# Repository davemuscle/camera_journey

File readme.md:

# Camera Journey Nonrelease - FPGA

*Migrated to Git on February 20th, 2022. Original release on May 23rd, 2021*.

This is my first “nonrelease”: a self-project that has no good output. I didn’t really have a clear
vision or goal of the project going into this, so there were a few unexpected twists, turns, and
burns. I like to think the journey and the things you learn along the way are more important than
having a pretty product at the end. We’ll see.

The general timeframe for this project was between November 2020 to May 2021. A good “vertical
slice” of the project was finished before New Years, and I took a few breaks after that. I gave a
few weeks to play(?) Skyrim, a few weeks to play Valheim, some time to goof around with a Discord
bot in Python, and some time to speedrun video games. There were also a lot of nights of just not
wanting to do anything technical after getting off work.

| Youtube Videos |
| :--: |
| *Camera Journey Nightmare* |
|  |

## Journey's Start
It all started when I bought another FPGA board after the Fractal Project (link). Instead of getting
another Xilinx board, I decided I was going to go back to Altera with the DE10-Nano by Terasic.
Altera chips were the ones we used in school for learning digital logic / design.

|  |
| :--: |
| *DE10-Nano from Terasic* |

The DE10-Nano is a nice SoC (System-on-Chip) board from Terasic for $150. It’s an FPGA coupled with
a CPU on the same chip.

The FPGA is a fairly sizable Cyclone V, with 110K LEs (4-input logic elements). The FPGA
architecture can also make use of Altera’s 8-input logic elements called ALMs. Equivalently, you get
40K ALMs. It would be a good data point to benchmark these and compare them to the flagship 6-input
LUTs of the 7series parts.

The CPU is a dual-core ARM Cortex A9 running at 800 MHz. It’s accompanied with an awesome 3500 page
manual of register descriptions (much less fun and interesting than FPGA architecture, huh!). Altera
refers to this part of the SoC as the HPS, the Hard Processor System.

## Twist One: The Pocket Synthesizer

The initial idea of the project was to make a handheld audio synthesizer. I’d slap a PCB with an
audio codec, a mini LCD, and a suite of input directly on top of the 2x20 male headers. I quickly
designed the schematic in KiCad, but ran into size constraints when picking out parts on DigiKey. If
it couldn’t have all the buttons I wanted, I wasn’t interested. So eventually this idea fizzled out.
The screenshot below is how far I got in the layout process of the PCB.

|  |
| :--: |
| *Plug-in Synthesizer End* |

## Twist Two: The Single Camera

I’ve had some experience working with camera modules, namely the OV5640 from Omnivision. I decided
that hooking up one of these to the DE10-Nano and then implementing some real-time video effects via
FPGA would be fun. I ended up buying one of Waveshare’s camera modules for $25. These versions of
the OV5640 are easier to use since they send data over a parallel video port, instead of MIPI.

|  |
| :--: |
| *Waveshare OV5640* |

The basic data flow idea was to have the camera send a raw 1920x1080 pixel stream at ~30 FPS into
the FPGA, buffer it, convert the Bayer sensor data to RGB, and send it to the HDMI sink. Here's the
hardware that had to be written to get the camera feed to show up on a TV or monitor:

|  |
| :--: |
| *FPGA Block Diagram for Single Camera Setup* |

- **OV5640 Controller**
    - Main controller that drives the design. It contains an SCCB (I2C) driver and a FIFO for sending register reads and writes to the camera during run-time. I had to rewrite the I2C driver used in the ADV7513 controller because Omnivision are dumb hacks. They copied the I2C bus and renamed it to SCCB to avoid paying royalties to Phillips. Problem with that is their device easily holds the bus hostage unless you give it special treatment.
- **DVP to AXI Video**
    - The start of the video datapath. Converts a parallel video port (HREF, VSYNC, 8 data bits) into AXI Video (SOF, EOL, Valid, 8 data bits).
- **Framebuffer**
    - Video buffering to provide a constant output stream at 1080p 60 FPS. Fun to design because there were three clock domains to handle.
- **Debayer**
    - Performs image demosaicing with multiple 5x5 sliding kernels. Converts raw sensor image data into the RGB colorspace
- **AXI Video to VGA**
    - Converts AXI video into VGA (HSYNC, VSYNC, DE, 24 data bits).
- **ADV7513 Controller**
    - Final output of the design. I2C commands initialize the ADV7513 chip by Analog Devices onboard the DE10-Nano. This handles the TMDS encoding and serialization of the VGA stream. Pretty easy chip to use and it's well documented.

## The Fun of Cameras

Like most other camera sensors, the documentation for the OV5640 is horrible or nonexistent. The
register maps have tons of hidden/reserved registers that are actually needed to get it to function
well. The manufacturers hide these registers expecting companies to purchase thousands of their
camera sensors, and sign an NDA with them for a user guide. Even after that, the user guide is in
broken English, and only works for certain camera setups. If you need to change camera settings or
resolutions, have fun. Although sparse, there is good documentation and drivers from users floating
around on Github and EEVblog. I had to spend a while to get these registers right, so I'm including
them in the references.

## The Framebuffer and the HPS

The most difficult part of the design was the frame buffering. Because standard monitors won’t
accept 1080p at 30 FPS, and because the camera frame rate isn’t exact, the input stream needs to be
buffered and read out at 1080p at 60 FPS. The answer to this is the triple-buffered frame buffer.

|  |
| :--: |
| *Framebuffer Design* |

For an uncompressed raw Bayer stream at 8 bits, that’s (1920\*1080\*8) 16.5 Mbits. The FPGA definitely
does not have enough block RAM for three frames of that. We could use the JPEG format on the camera
sensor to reduce this, but I don’t want to imagine the horror of getting that setup. We could also
do the JPEG encoding/decoding in the FPGA, but for some reason I didn’t want to do that (in
retrospect, it’s not a bad idea). This leaves the only available memory option as the DDR3 onboard
the DE10-Nano.

The idea of my framebuffer is to have three buffers being used in memory. Two buffers will always be
used for writing, and one for reading. The arbiter manages the buffers such that the one being read
from is never written into.

The memory controller allows a wide data width of 256 bits, so incoming pixels are packed up and
written into the first asynchronous FIFO. A pulse is driven and syncronized to the memory clock
domain telling the arbiter to start moving that line into the DDR3. Once a full frame is written,
the arbiter allows a downstream timer to read lines at the rate required for the output resolution.
The output pixels are unpacked and then sent downstream.

Accessing the DDR3 from the FPGA on the Cyclone V is a bit strange, and it was definitely a
challenge for me. At this point I had written all the RTL for the FPGA, and hadn’t even touched the
HPS. The only way to access the DDR3 through the FPGA is to get the HPS programmed and have it
enable the bridge from the hardened memory controller to the FPGA, so here we go.

If you want to use the HPS in your FPGA design, you need to instantiate it as a component in Qsys.
Qsys is comparable to Xilinx’s IP integrator for block designs. I didn’t want to take any chances,
so I modified the Qsys file given by the golden reference design by Terasic. The part of note when
creating the Qsys was enabling the fpga2sdram bridge. This gives the FPGA access to the memory
controller. I programmed the SDcard given with the DE10-Nano with Terasic’s known-good image for
DDR3 communication, and was ready to go.

|  |
| :--: |
| *Qsys Instantiating the HPS* |

My first iteration of the framebuffer used the Avalon interface to talk to the SDRAM controller.
Avalon is much simpler compared to AXI: there are a lot less signals and it’s pretty easy to
implement. My main problem with it was that the memory controller would lock up if I tried to do
even small bursts, like a burst of 8. So my design could only request one transaction at a time.
This was fine because of the interface's wide bus width of up to 256 bits.

I now had a real-time camera stream going to my TV from the OV5640. After adding a weird
font-overlay controller in RTL, I made a backup of the project, and took a break. This was on
December 31st 2020. Unfortunately I never recorded a demo video of this stage of the project, since
I didn’t think much of it.

After taking a break for maybe a month, I decided to come back and make some upgrades. I rewrote the
framebuffer entirely, made it more modular, and converted the bus from Avalon to AXI. This means I
had to change the fpga2sdram bridge in the HPS from Avalon to AXI. I also added in memory addressing
options, to provide vertical and horizontal effects like splitscreen, flip, mirror, and scrolling.

## The Preloader and U-Boot

I came across a major problem with my upgraded framebuffer -- I couldn’t write to it! The SDRAM
controller was never responding to my ‘awvalid’ requests. With some research, I decided that the
problem was because I needed to update the preloader or update U-Boot for the HPS. Below are
conceptual designs for the most important hardware chunks of the fractal engine: the fractal slice,
and the fractal core. 

The Cyclone V has a pretty involved boot process. First it reads from an onboard ROM for boot
information, then it reads from the preloader within the SDcard, then it reads from U-Boot, which is
also in the SDcard. After that, it finally loads up Linux.

Apparently, if you make some drastic changes to the HPS in Qsys, you need to subsequently update the
preloader, whoops! I started reading documentation on building embedded linux for the Cyclone V, and
tutorials from Rocketboards on rebuilding the preloader. Nothing was working for me though. I
downgraded my Quartus and SoC EDS versions to match what was used for the reference design, and
tried a whole suite of things. All the tutorials I was looking at were using Linux to rebuild the
preloader, and I was working in Windows, so I chalked it up to that.

There is a single post on the Intel forums that is dealing with this issue, where the AXI writes
don’t respond. In that post they say to update the preloader or update U-Boot: so it was time to try
U-Boot.

|  |
| :--: |
| *Intel Forum Post* |

After looking into how U-Boot works, I plugged in the USB cable from the DE10-Nano into my PC,
opened PuTTy as a serial port at 115200 / 8bits / no parity, and booted it up. I pressed a key to
stop the autoboot and typed in “printenv” to see the U-Boot setup. U-Boot uses a bunch of
environment variables stored in the SDcard to configure the HPS after the preloader. To my surprise,
this fpga2sdram_handoff variable seemed funky.

According to the Cyclone V manual, the AXI bridges require two ports (compared to Avalon bridges
requiring one port) of the SDRAM controller. The default U-Boot script was holding my AXI port in
reset!

|  |
| :--: |
| *U-Boot Environment Variable Snippet* |

|  |
| :--: |
| *Cyclone V Holding My AXI Port Hostage!* |

I added a single line to my U-boot script and placed it on the SDcard. Done, my upgraded framebuffer
was working great.

|  |
| :--: |
| *Fixed U-Boot Script* |

## Image Processing Verification Tools

To make verification of my video processing blocks better, I designed some VHDL blocks to easily
facilitate passing image data through a testbench. I use a MATLAB script to convert RGB images from
any filetype into a flattened text file of integers. The image_reader block within the
pattern_generator block reads this text file and provides it as an AXI video stream. The pattern
generator can also give counting patterns, or two types of standard color bars. 

The image data is passed through the DUT and then sent into the image_writer block, producing
another text file. Outputs are given to stop the testbench when a certain number of images have been
written. I then have another script in MATLAB that converts the text file back to an image, and
plots it on the screen. It can then be visually inspected to verify RTL image processing.

The image_writer and image_reader blocks accomplish this by using std.textio library to read and
write files. The way I’m using the std.textio library here is not synthesizable. This is meant only
for simulation. However, you can synthesize with this library! But it’s only to initialize BRAM, it
only works in Vivado, and it only works if the text files are of the bit_vector type. I did this in
my 96-Note Spectrum Analyzer.

|  |
| :--: |
| *Testbench with Image Verification Suite* |

|  |
| :--: |
| *You can get some pretty funky outputs with a buggy FPGA design! This was created due to a FIFO underflow while simulating my debayer block.* |

## Python Control via UART

An interesting idea I had for debugging my FPGA designs was to hook up a UART-USB converter and use
PySerial to send scripted reads/writes over a serial port. I picked up a converter from Digilent and
wrote some RTL for a UART driver. 

|  |
| :--: |
| *Digilent's PMOD UART to USB* |

Writing the RTL for serial interfaces like I2C, SPI, and UART are easy enough. The major part that I
overlooked was how UART expects bits LSB first, but pretty quickly I could read and write a register
using Python code. I set up a basic communication structure with byte stuffing so that PySerial
could send packets, giving it 32-bit access to a 16-bit address space.

I then came up with a commenting format, which would be written inside the VHDL register file. The
comments would describe various register descriptions, bit fields, and address offsets. A different
Python script would parse through the register file, and auto-generate a suite of classes that could
be imported and used for easily accessing FPGA registers without having to remember address offsets
or bitfield locations.

Description | Image
:--: | :--: 
VHDL Register File with Comments for Parsing |  
Generated FPGA Class |  
Generated Register Class | 
Using iPython | 
Help Command for the FPGA | 
Help Command for the Registers | 
iPython with tab auto-completion | 
Writing to all 32-bits of a register | 
Writing to a single bitfield of a register | 

Was there a better way to do this? For sure. If I ever decide to use Python again for this, I’ll use
XML-type formatting in the RTL to standardize things instead of using my own format. Is this kind of
an abuse of the Python class construct? Ha, yeah!

## Twist Three: The Double Cameras
One of the main projects floating around online for the DE10-Nano is a “Real-time HDR Video”
project. It’s even packaged with the System-CD by Terasic. The idea involves feeding two camera
streams into the FPGA with differing exposure settings. The streams are then mixed together to give
a single feed but with a higher dynamic range. I decided I wanted to do something similar. Maybe use
two cameras to emulate our brain’s depth perception, or do some parallax effect.

I designed a PCB in KiCad to hold two cameras, sent it off, and had it back in a week or so. It’s a
really simple board that just plugs into one of the 2x20 headers on the DE10-Nano, and then two
Waveshare cameras plug into the PCB to give two streams. When I made the PCB, I also included a
design to hold four cameras, just in case I wanted to try and do something with 360 degree coverage.

 | 
:--: | :--:
*Camera Board PCB* | *Dual Camera Board in Action*

The PCB worked fine, but the Waveshare camera modules definitely were not behaving the way I
expected. Two OV5460 camera modules with the same external input clocks, same I2C inputs, and same
register initializations do not behave the same way!

My first approach to fix this was using an asynchronous FIFO to match the rates, IE: if one camera
sent their start-of-frame 10 clocks early, then it was delayed and the proper CDC was applied to
make sure the streams lined up. The biggest problem with this was the skew between frames. Both
cameras need to be running at exactly the same FPS, and that just won’t happen. Eventually the skew
would cause the FIFO to overflow, and then it’s over. The reference project does some hack where
they lower the external clock rate of one camera for a short amount of time, but I don’t like that.

 | 
:--: | :--:
*Dual Camera Skew* | *Awful Camera Noise*

The best solution for me would be to upgrade the framebuffer to support multiple channels. So I did.
But then Qsys reported the HPS couldn’t support multiple AXI channels, so I’d need to either write
an interconnect or downgrade back to the Avalon bus. This annoyed me, so I started evaluating
options.

The quality of the camera streams wasn’t even good: they were filled with intensive raw pixel noise.
Even my work with just one of the camera modules suffered from this. I tried tons of register
configurations and couldn’t get the noise to go away. The OV5640 manual lists a maximum of 3.0V on
the digital IO, but Waveshare is driving them with 3.3V, maybe that’s it? The horrible Waveshare
board is also driving IO pins directly to 3.3V and GND (seriously, look that up), maybe that's it?
The DVP mode is a parallel video bus running at ~80 MHz, so there is probably extreme crosstalk
happening between the data bits, maybe that’s it? 

Either way, I wasn’t too excited about working more with these camera modules. It was time to move
on. At least I had got my demo to the point of being able to switch between camera streams. In the
GIF below you can see the parallax effect for a flash drive closely in front of both cameras. This
is the same thing as putting your thumb in front of your face, then alternating between which eye
you have open.

:--:
*Camera Parallax*

## Twist Four: The IP Camera

This DE10-Nano board has a few interesting peripherals connected only to the HPS: ethernet, USB-OTG,
and an accelerometer. So far, the entire project hasn’t touched these because I’ve stayed away from
the HPS. Not anymore, I’m diving right in!

The new idea was to buy an IP camera from Amazon, plug it into the ethernet port on the DE10-Nano,
and have a Linux image loaded onto the ARM CPU to pull from the camera. I could then use the FPGA to
apply video effects, then send it over the USB port to my PC as a UVC Webcam.

I bought a cheap camera, plugged it into my router, and logged into its HTML page. This was so
refreshing just being able to mouse around and change the camera settings, instead of sending
commands over an I2C bus! I made sure the camera wasn’t DOA by viewing the feed in Internet
Explorer.

:--:
*IP Security Camera*

After making sure the IP address was static, I connected the camera directly to the DE10-Nano and
started poking around in Linux. I wanted to see packets being sent that carried the video data, even
if I couldn’t view the frames. I used ifconfig and tcpdump to try and read packets. The main thing I
could see was the camera asking for a MAC address over ARP.

:--:
*Viewing Packets and ARP Requests*

Even after making sure the ARP was set up correctly, I could tell the camera wasn’t sending enough
data for a video stream. So there is some initialization that needs to happen here. I put the camera
back into the router, and used Wireshark on my main PC to see what was happening.

 | 
:--: | :--:
*Slow Packets with No Video | RTSP Packets using UDP to Send Video*

I determined that I shouldn’t be thinking about this in such a low-level way. Eg: I don’t need to
manually construct the TCP packets to initialize this. There is already software to do it all. With
research, FFmpeg seemed like the way to go.

## H264 and FFMPEG

FFMPEG is a FOSS library for performing various video processing applications. Most specifically,
with the installation of libx264, it could read H.264 encoded video over an RTSP stream. This is
exactly what my camera is sending, so I started working on getting FFmpeg installed.

The Linux distribution that Terasic gives with the System-CD is Angstrom. I tried using ‘opkg’ to
install FFmpeg, but it wasn’t giving me anything usable. I also didn’t see an option for libx264. So
I decided to compile it from source.

I used GIT to pull both sets of source codes, and started running Makefiles. I followed some
instructions online and had to manually modify a few paths. Libx264 compiles pretty quickly, but
FFmpeg was taking a few hours. FFmpeg also failed about an hour due to memory constraints, so I
plugged in a 16GB flash drive, mounted it in Linux, and compiled it under there. Eventually I had a
usable FFmpeg binary.

**Editor's note 02/20/2022: Cross compiling here would have been a better choice**

:--:
*Compiling FFmpeg with an SD card*

FFmpeg could now pull a single frame from the camera and convert it into JPG. I opened an SFTP
session within MobaXterm to view the image over windows by just double clicking it. Even if it’s out
of focus, it’s looking good! Much less painful than the OV5640. I also tested FFmpeg by converting a
view seconds of the stream into an MP4, and it worked decently well. It was a bit slow though.

:--:
*Capturing a Still with FFmpeg*

:--:
*Bonus: Security camera trying to send data back to China. Hope you enjoyed the bathrobe show.*

## Hardware Software Bridge

The next step was to get the IP camera feed to show up on my HDMI monitor/TV. This required
functional communication between the HPS and FPGA. I quickly converted my framebuffer into a
framestreamer, which would only read from the DDR3 and let the HPS fill the memory with what should
be shown on the screen. I also added some AXI ports in the Qsys to allow the HPS to control the
framestreamer parameters like the frame offsets, which frame number is active, and the resolution of
the frame. These AXI ports would connect the FPGA to the HPS via the “lighweight AXI bridge”, which
was viewable in the device tree.

:--:
*Simpler FPGA Design to Leverage SW*

It was quite a breath of fresh air writing C code for this. I memory mapped the lightweight bridge,
and three portions of memory in DDR3 for the three triple-buffered frames. My first check was to
fill that image-space and make sure it would show up on the screen. On my Windows PC I converted a
JPG image to a binary file, then used C code on the DE10-Nano to write the binary file into DDR3
memory. The output is below.

:--:
*C code snippet to copy the binary file into shared SDRAM*

:--:
*HW SW Bridge in Action: Software Sets Up the Image, Hardware Displays it*

## Journey's End

Things fell apart when I wanted to see the real-time security camera video on the monitor. The ARM
CPU was just not keeping up with the requirements to read the RTSP packets, decode the H264 stream,
and convert it to raw RGB video. I checked the CPU usage with “htop”, and both were at 100%. The
FPGA also wasn’t helping, because it has to take priority over the memory controller to read the
frames at a constant rate. Since the memory controller arbitrates access to the FPGA and HPS, there
is some slowdown here. Even with a lower resolution I couldn't get a good output.

I had hit the limit, and was out of ideas. This camera was definitely not right for the project
goals (if there ever were any), and I had enough with the twists and turns, so I called it quits.
The video shown at the top and on the front page was the farthest I got with this camera. There were
definitely still improvements needed to the C code and FPGA design.

I take a lot of pride in having the grit to push through issues and never giving up, but the idea of
moving on and doing something new is too exciting. So this marked the end of the camera journey.

 | 
:--: | :--:
*IP Camera Setup to DE10-Nano Embedded Linux* | *Glitchy, High Latency, ~1FPS IP Camera Output*

## In Retrospect

Here are various things that I got some exposure to, designed, or enjoyed doing:
- Serial interfaces like UART and I2C 
- Debayer RTL block
- Framebuffer RTL block
- Asynchronous FIFOs, handshake-based pulse synchronizers, CDC with >2 clock domains
- Video verification techniques, testbench improvements
- Python generated classes for FPGA control
- Quartus flow (even if it was just clicking in the GUI)
- Quartus Qsys Design, using Altera IP (PLLs)
- U-Boot
- Embedded Linux
- Basic Networking (I'm still a baby - but this was good to learn)
- Real C-code (memory mapping, malloc, free)

Here are some of the ideas I had that didn't pan out, or that I didn't get to:
- Ray-tracing
- Face Detection via Viola Jones (did a lot of MATLAB studying on this, but struggled with it. Neural network next time)
- Real-time Video Fx in RTL
- Stereoscopics

Here are some of the things I didn't like:
- Altera/Intel Documentation, lack of active forum compared to Xilinx
- Cyclone V preloader issues

**Editor's Note, 02/20/2022: Looks like Xilinx forums are going in a similar direction?**

## Downloads
- [OV5640 Init Sequence for 1080p DVP Mode](/doc/ov5640_init.txt)
- [ADV7513 Init Sequence for DE10-Nano at 24-bit RGB 1080](/doc/adv7513_init.txt)

## References
1. [Terasic, DE10-Nano Kit Downloads](https://www.terasic.com.tw/cgi-bin/page/archive.pl?Language=English&No=1046&PartNo=4)
2. [Analog Devices, ADV7513 Programming Guide](https://www.analog.com/media/en/technical-documentation/user-guides/ADV7513_Programming_Guide.pdf)
3. [Waveshare (hooligans), OV5640 Board](https://www.waveshare.com/wiki/OV5640_Camera_Board_(B))
4. [Sparkfun, OV5640 Manual](https://cdn.sparkfun.com/datasheets/Sensors/LightImaging/OV5640_datasheet.pdf)
5. [Xenpac/sun4csi, Great OV5640 Driver](https://github.com/xenpac/sun4i_csi/blob/master/device/ov5640.c)
6. [Standford, High-Quality Linear Interpolation For Demosaicing of Bayer-Patterned Color Images](https://stanford.edu/class/ee367/reading/Demosaicing_ICASSP04.pdf)
7. [Altera, Avalon Bus Spec](http://www1.cs.columbia.edu/~sedwards/classes/2011/4840/mnl_avalon_spec.pdf)
8. [ARM, AXI Bus Spec](http://www.gstitt.ece.ufl.edu/courses/fall15/eel4720_5721/labs/refs/AXI4_specification.pdf)
9. [Intel Forum, How can I enable the FPGA2SDRAM bridge on Cyclone V SOC devices?](https://www.intel.com/content/www/us/en/support/programmable/articles/000086918.html)
10. [Criticallink.com, Important Note about FPGA/HPS SDRAM Bridge](https://support.criticallink.com/redmine/projects/mityarm-5cs/wiki/Important_Note_about_FPGAHPS_SDRAM_Bridge)
11. [Oguz Meteer, Building embedded Linux for the Terasic DE10-Nano](https://bitlog.it/20170820_building_embedded_linux_for_the_terasic_de10-nano.html)
12. [Altera, Cyclone V HPS TRM](https://www.intel.com/content/dam/www/programmable/us/en/pdfs/literature/hb/cyclone-v/cv_54001.pdf)
13. [Wimsworld, New FFMPEG install on BeagleBone Black](https://wimsworld.wordpress.com/2013/06/26/new-ffmpeg-install-on-beaglebone-black/)
14. [Batchloaf, A simple way to read and write audio and video files in C using FFmpeg](https://batchloaf.wordpress.com/2017/02/12/a-simple-way-to-read-and-write-audio-and-video-files-in-c-using-ffmpeg-part-2-video/)

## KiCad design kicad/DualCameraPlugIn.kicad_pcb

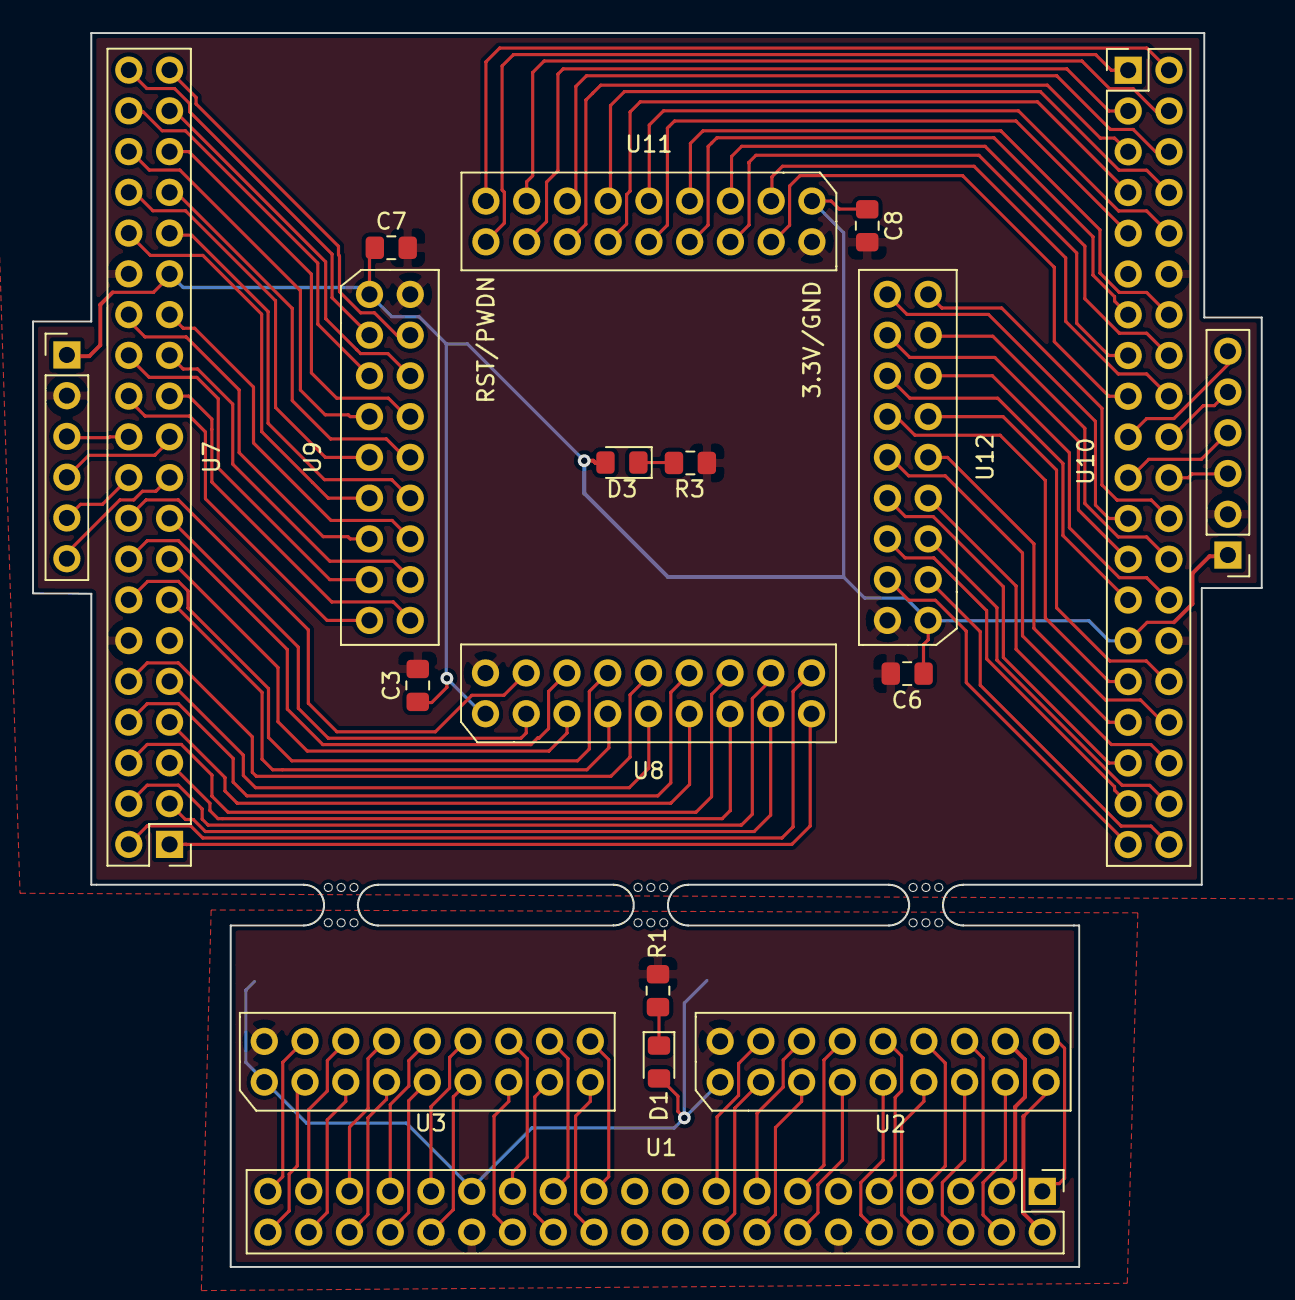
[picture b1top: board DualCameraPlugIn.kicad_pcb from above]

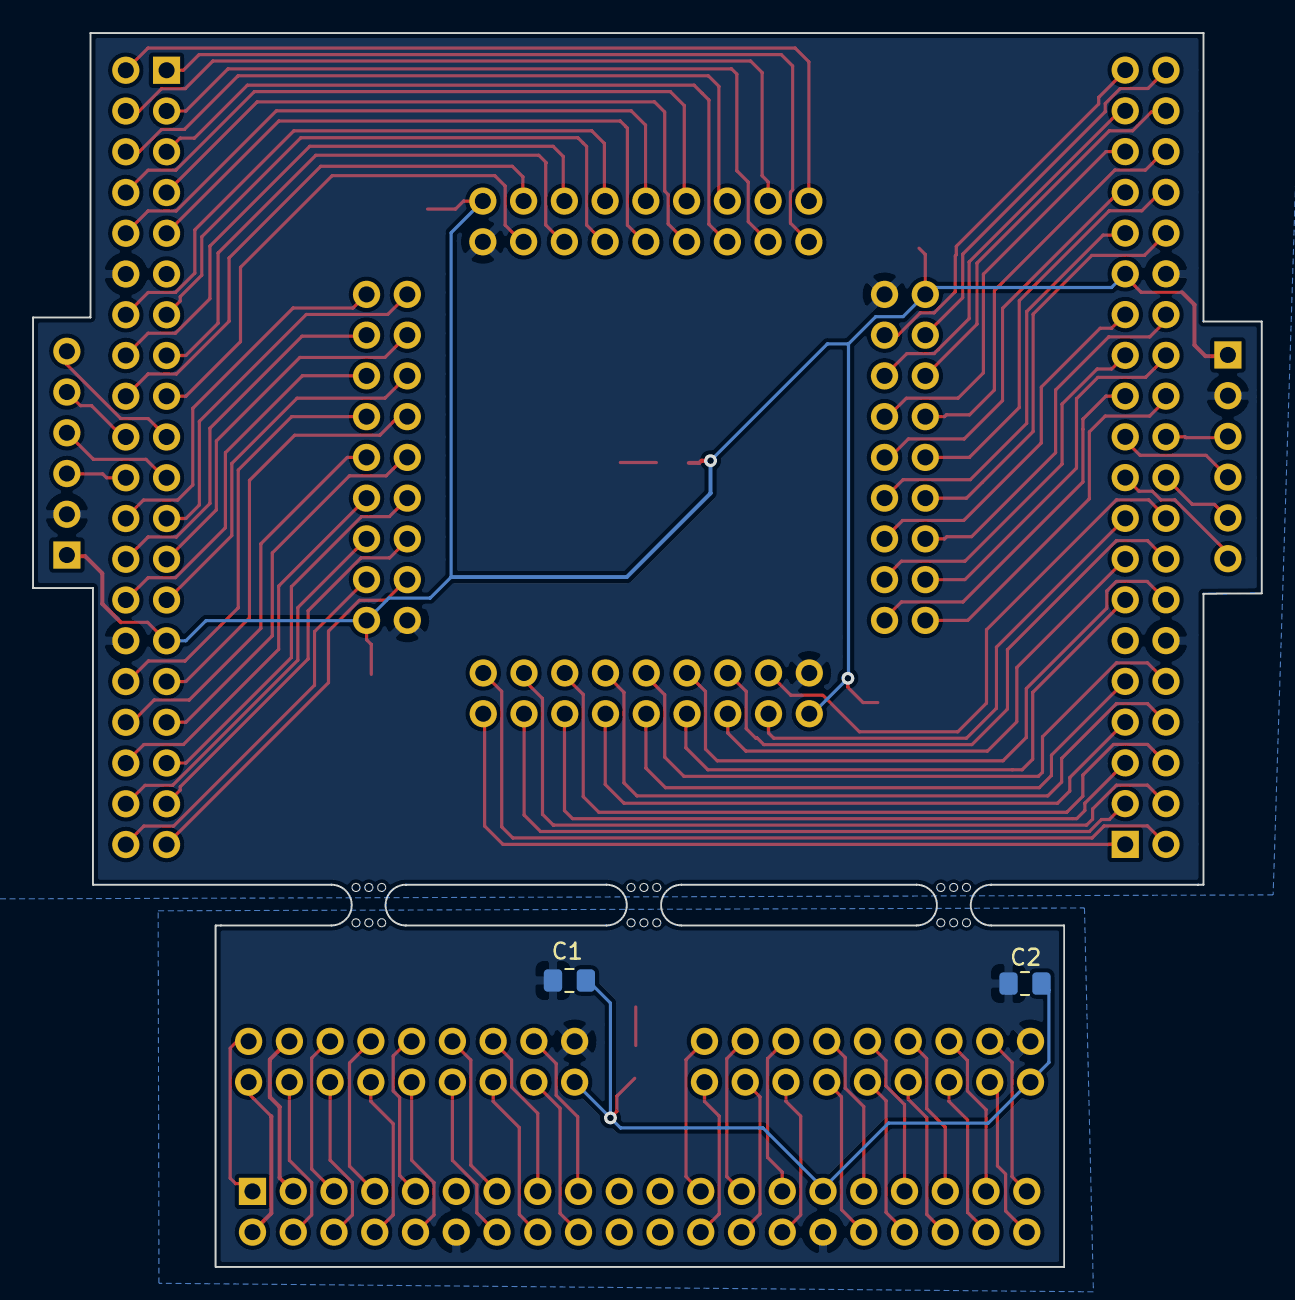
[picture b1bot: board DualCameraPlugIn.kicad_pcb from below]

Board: 2 copper layers, 76.6 x 76.9 mm, 24 parts (2 on the bottom side), 110 nets.

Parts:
C1, C2, C3, C6, C7, C8: 0.1u; C_0805_2012Metric_Pad1.15x1.40mm_HandSolder
D1, D3: LED; LED_0805_2012Metric_Pad1.15x1.40mm_HandSolder
J1, J2: Conn_01x06; PinHeader_1x06_P2.54mm_Vertical
R1, R3: R; R_0805_2012Metric_Pad1.15x1.40mm_HandSolder
U1, U7: DE10-Nano-GPIO1; PinHeader_2x20_P2.54mm_Vertical
U2, U3, U8, U9, U11, U12: Waveshare_OV5640_DVP; WaveshareOV5640
U10: DE10-Nano-GPIO0; PinHeader_2x20_P2.54mm_Vertical
mouse-bite-2.54mm-slot, mouse-bite-2.54mm-slot#2, mouse-bite-2.54mm-slot#3: VAL**; mouse-bite-2.54mm-slot

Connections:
+3V3: C3.1, C6.1, C7.1, C8.1, D3.2, J1.1, J2.1, U7.29, U8.1, U9.1, U10.29, U11.1, U12.1
+3V3_CAM1: C1.1, C2.1, D1.2, U1.29, U2.1, U3.1
/DualCamera/CAM1_A_D2: U1.3, U2.16
/DualCamera/CAM1_A_D3: U1.4, U2.15
/DualCamera/CAM1_A_D4: U1.5, U2.14
/DualCamera/CAM1_A_D5: U1.6, U2.13
/DualCamera/CAM1_A_D6: U1.7, U2.12
/DualCamera/CAM1_A_D7: U1.8, U2.11
/DualCamera/CAM1_A_D8: U1.9, U2.10
/DualCamera/CAM1_A_D9: U1.10, U2.9
/DualCamera/CAM1_A_HREF: U1.15, U2.6
/DualCamera/CAM1_A_PCLK: U1.14, U2.7
/DualCamera/CAM1_A_PWDN: U1.1, U2.18
/DualCamera/CAM1_A_RESET: U1.2, U2.17
/DualCamera/CAM1_A_SIOC: U1.18, U2.3
/DualCamera/CAM1_A_SIOD: U1.17, U2.4
/DualCamera/CAM1_A_VSYNC: U1.16, U2.5
/DualCamera/CAM1_A_XCLK: U1.13, U2.8
/DualCamera/CAM1_B_D2: U1.25, U3.16
/DualCamera/CAM1_B_D3: U1.26, U3.15
/DualCamera/CAM1_B_D4: U1.27, U3.14
/DualCamera/CAM1_B_D5: U1.28, U3.13
/DualCamera/CAM1_B_D6: U1.31, U3.12
/DualCamera/CAM1_B_D7: U1.32, U3.11
/DualCamera/CAM1_B_D8: U1.33, U3.10
/DualCamera/CAM1_B_D9: U1.34, U3.9
/DualCamera/CAM1_B_HREF: U1.37, U3.6
/DualCamera/CAM1_B_PCLK: U1.36, U3.7
/DualCamera/CAM1_B_PWDN: U1.23, U3.18
/DualCamera/CAM1_B_RESET: U1.24, U3.17
/DualCamera/CAM1_B_SIOC: U1.40, U3.3
/DualCamera/CAM1_B_SIOD: U1.39, U3.4
/DualCamera/CAM1_B_VSYNC: U1.38, U3.5
/DualCamera/CAM1_B_XCLK: U1.35, U3.8
/QuadCamera/CAM0_A_D2: U10.3, U11.16
/QuadCamera/CAM0_A_D3: U10.4, U11.15
/QuadCamera/CAM0_A_D4: U10.5, U11.14
/QuadCamera/CAM0_A_D5: U10.6, U11.13
/QuadCamera/CAM0_A_D6: U10.7, U11.12
/QuadCamera/CAM0_A_D7: U10.8, U11.11
/QuadCamera/CAM0_A_D8: U10.9, U11.10
/QuadCamera/CAM0_A_D9: U10.10, U11.9
/QuadCamera/CAM0_A_HREF: U10.15, U11.6
/QuadCamera/CAM0_A_PCLK: U10.14, U11.7
/QuadCamera/CAM0_A_PWDN: U10.1, U11.18
/QuadCamera/CAM0_A_RESET: U10.2, U11.17
/QuadCamera/CAM0_A_SIOC: U10.18, U11.3
/QuadCamera/CAM0_A_SIOD: U10.17, U11.4
/QuadCamera/CAM0_A_VSYNC: U10.16, U11.5
/QuadCamera/CAM0_A_XCLK: U10.13, U11.8
/QuadCamera/CAM0_B_D2: U10.25, U12.16
/QuadCamera/CAM0_B_D3: U10.26, U12.15
/QuadCamera/CAM0_B_D4: U10.27, U12.14
/QuadCamera/CAM0_B_D5: U10.28, U12.13
/QuadCamera/CAM0_B_D6: U10.31, U12.12
/QuadCamera/CAM0_B_D7: U10.32, U12.11
/QuadCamera/CAM0_B_D8: U10.33, U12.10
/QuadCamera/CAM0_B_D9: U10.34, U12.9
/QuadCamera/CAM0_B_HREF: U10.37, U12.6
/QuadCamera/CAM0_B_PCLK: U10.36, U12.7
/QuadCamera/CAM0_B_PWDN: U10.23, U12.18
/QuadCamera/CAM0_B_RESET: U10.24, U12.17
/QuadCamera/CAM0_B_SIOC: U10.40, U12.3
/QuadCamera/CAM0_B_SIOD: U10.39, U12.4
/QuadCamera/CAM0_B_VSYNC: U10.38, U12.5
/QuadCamera/CAM0_B_XCLK: U10.35, U12.8
/QuadCamera/CAM1_A_D2: U7.4, U8.16
/QuadCamera/CAM1_A_D3: U7.3, U8.15
/QuadCamera/CAM1_A_D4: U7.6, U8.14
/QuadCamera/CAM1_A_D5: U7.5, U8.13
/QuadCamera/CAM1_A_D6: U7.8, U8.12
/QuadCamera/CAM1_A_D7: U7.7, U8.11
/QuadCamera/CAM1_A_D8: U7.10, U8.10
/QuadCamera/CAM1_A_D9: U7.9, U8.9
/QuadCamera/CAM1_A_HREF: U7.16, U8.6
/QuadCamera/CAM1_A_PCLK: U7.13, U8.7
/QuadCamera/CAM1_A_PWDN: U7.2, U8.18
/QuadCamera/CAM1_A_RESET: U7.1, U8.17
/QuadCamera/CAM1_A_SIOC: U7.17, U8.3
/QuadCamera/CAM1_A_SIOD: U7.18, U8.4
/QuadCamera/CAM1_A_VSYNC: U7.15, U8.5
/QuadCamera/CAM1_A_XCLK: U7.14, U8.8
/QuadCamera/CAM1_B_D2: U7.25, U9.16
/QuadCamera/CAM1_B_D3: U7.26, U9.15
/QuadCamera/CAM1_B_D4: U7.27, U9.14
/QuadCamera/CAM1_B_D5: U7.28, U9.13
/QuadCamera/CAM1_B_D6: U7.31, U9.12
/QuadCamera/CAM1_B_D7: U7.32, U9.11
/QuadCamera/CAM1_B_D8: U7.33, U9.10
/QuadCamera/CAM1_B_D9: U7.34, U9.9
/QuadCamera/CAM1_B_HREF: U7.37, U9.6
/QuadCamera/CAM1_B_PCLK: U7.36, U9.7
/QuadCamera/CAM1_B_PWDN: U7.23, U9.18
/QuadCamera/CAM1_B_RESET: U7.24, U9.17
/QuadCamera/CAM1_B_SIOC: U7.40, U9.3
/QuadCamera/CAM1_B_SIOD: U7.39, U9.4
/QuadCamera/CAM1_B_VSYNC: U7.38, U9.5
/QuadCamera/CAM1_B_XCLK: U7.35, U9.8
/QuadCamera/EX1: J2.3, U7.22
/QuadCamera/EX2: J2.4, U7.21
/QuadCamera/EX3: J2.5, U7.20
/QuadCamera/EX4: J2.6, U7.19
/QuadCamera/EX5: J1.3, U10.22
/QuadCamera/EX6: J1.4, U10.21
/QuadCamera/EX7: J1.5, U10.20
/QuadCamera/EX8: J1.6, U10.19
GND: C3.2, C6.2, C7.2, C8.2, J1.2, J2.2, R3.2, U7.12, U7.30, U8.2, U9.2, U10.12, U10.30, U11.2, U12.2
GND_CAM1: C1.2, C2.2, R1.2, U1.12, U1.30, U2.2, U3.2
unnamed: D1.1, R1.1
unnamed: D3.1, R3.1

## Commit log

2022-02-21 initial migration
2022-02-21 test 2x3 table
2022-02-21 test 2x3 table 2
2022-02-21 test 2x3 table 3
2022-02-21 test 2x3 table 4
2022-02-21 finished up readme
2022-02-21 fix minor details
2022-02-21 cleanup python dir
2022-02-22 fix parallax gif
